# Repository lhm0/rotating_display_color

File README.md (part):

# Rotating Color Display

## Abstract: 
 The Rotating Color Display is a compact disc-sized device that rotates quietly using a CD motor. It features 56 color LEDs that display animated color images as well as time and weather data sourced from the internet. The device is wirelessly powered and controlled via a user-friendly web interface. It uses ESP32 and RP2040 microcontrollers, pre-manufactured boards, and is easy to assemble.

<p align="center"> 

</p> 

## 1. Description of the device

The Rotating Color Display device comprises two primary units: a power supply unit and a display board (**figure 1**). Both are circular in design, with a diameter of 120mm, similar to the dimensions of a standard Compact Disk. The display board is rotated by a CD motor. Energy is wirelessly transmitted from the power supply unit to the display board, eliminating the need for wired connections.

**Figure 1:  Rotating Color Display assembly.** The lower PCB is the power supply with wireless power transmission, the upper PCB is the display board.

The display board is equipped with a row containing 56 color LEDs. The LED operations are controlled by a RP2040 microcontroller, while an ESP32 microcontroller generates the display content. Images (including animated images) can be stored on and loaded from a micro SMD card. The ESP32 maintains a Wi-Fi connection to the internet.

This internet connection allows the device to retrieve the time from a time server, ensuring time accuracy. It also allows for the acquisition of weather data. Device operation is managed through a web interface (**figure 2**), accessible from any web browser. The interface allows users to manage login credentials, upload image files to the display, and control image and configuration files through a file manager.

**Figure 2:** The **web user interface** allows for operating mode selection and device configuration.

## 2. Operating modes

When switched on, the device tries to connect to a known wifi. If no valid wifi credentials are found, the unit will be configured as wifi access point. In this mode, a computer or mobile device can be connected, directly (SSID: RD40, no password). 

Once the wifi connection has been established, the unit will display its IP address on the  home page of the device (**figure 3**). Enter this address in your web browser. This will load the web user interface and will allow you to configure your local wifi.

**Figure 3: home page.**

There are several operating modes that display time and weather information (**figure 4**). The logo clock mode integrates a customizable image into the clock face. The image can be easily uploaded from the user interface. The same is true for the analog clock, which uses a customizable clock face in the background.

**Figure 4: operating modes.** Modes can be selected and configured through the web interface.

## 3. Mechanical design

The device consists of two assemblies: power supply and display. The power supply board is also the base plate, which can either be placed on a flat surface or hung on a wall. A standard CD motor is attached to this board so that the CD tray above the power supply board can accommodate the display assembly. The display board is fixed with two M2 x 6 mm screws. Furthermore, the base plate carries a potentiometer to control the motor speed as well as an on/off switch for the motor.

**Figure 5: Power Supply Board** with CD motor (middle), 12 - 24 V power jack (lower side), and speed potentiometer

An important requirement for the display board is that the center of mass of the unit is exactly in the middle, on the axis of rotation of the motor. This is the only way to ensure smooth and vibration-free running of the display. To achieve this, the electronic components are arranged symmetrically in three groups (**figure 7**). In the first group the components are arranged symmetrically to a vertical axis. This initially ensures that the center of gravity lies on this vertical axis. However, since the components cannot be distributed symmetrically to the horizontal axis of symmetry, the center of gravity must be shifted to the center along this axis using balancing weights. For this purpose, two M3x6mm screws with two nuts each are placed to the right and left of the ESP32 antenna. The second group of components is arranged symmetrically in respect to the center point of the disk and does not need a balancing weight, therefore. The third group, however, does need a balancing weight (M3 x 6, 1 nut) in the 4:30 position of the disk.The overall balancing result is very good, but can certainly be further optimized.

**Figure 6: Display Board.** Main components are the two LED rows, five serial shift register chips, and two microcontrollers (Arduino nano and ESP-01s). On the backside of the board the secondary coil of the wireless power supply is attached.

**Figure 7:** The components of the display board are arranged symmetrically in three groups. Balancing weights are used in group 1 and 3 to shift the center of gravity to the middle of the disk.

The LED row consists of 56 discrete, rectangular LEDs. The components each have a width of 1.6 mm and can be lined up with little spacing. The center of the LEDs is in a 2 mm grid. However, the row of LEDs is not arranged symmetrically to the center of the disk, but shifted by 0.5 mm. If the display panel is rotated by 180 degrees, this decentration causes the LEDs to be shifted by exactly 1 mm from the original grid (**figure 8**). This results in rotational interlacing: the radial resolution is increased from 2 to 1 mm. At the same time, the perceived frame rate also increases by a factor of 2..

**Figure 8:** The LED row is shifted radially by half a LED width. The two halfs of the row generate an interlacing effect, which doubles both the radial resolution and the image frame rate.

The LEDs must output the image information at exactly the right position with each rotation. For spatial alignment of the image, a trigger signal is generated at a defined position for each rotation, which triggers the sequential, clocked output of the pixels. The trigger signal must be spatially very stable, otherwise no smooth image can be generated. It turned out that a Hall sensor is best suited for this purpose. It is located between the two USB-C connectors (see **figure 6**, left picture, bottom edge of the PCB). The magnet is glued into a hole of the power supply PCB (see figure 5, right picture, 2 o'clock position).

## 4. Electronics architecture

The distribution of the electronic circuitry between the two assemblies is shown in **figure 9**. The power supply assembly contains a Royer converter for wireless power transfer to the display assembly and an adjustment of the motor speed. The 56 color LEDs of the display assembly are controlled by 7 shift registers (24 bits each), which in turn are supplied with clock and data by a RP2040 microcontroller via an SPI interface. The displayed content is generated by an ESP32-S3 microcontroller, which is connected to the internet via Wifi. Furthermore, image data can be loaded from a micro SD card. The ESP32 transmits its data to the RP2040 via a SPI interface.

**Figure 9: electronics schematics.**

## 5. Power supply board

The core of the power supply is a Royer converter for wireless power transfer. An excellent article on the operation and design of the circuit can be found at Mikrocontroller.net (German) and the circuit was taken from there. Two transistors are alternately switched (push pull operation) so that a current flows through one half of the coil at a time. The coil belongs to a resonant circuit with a resonant frequency of about 120 kHz. The control voltage for the transistors is obtained via a coupling coil (**figure 10**). The secondary coil is located below the display board (see **figure 6**, right).

The Royer circuit uses very few components. However, the coil is quite complex. It is a bifilar coil, where the two halves are interleaved. In addition, the coupling coil must be connected with the correct polarity, otherwise the two transistors will be destroyed. In the early stages of development, the coil was wound with copper wire. However, this solution was quite difficult to reproduce, so in the final design the coils (bifilar primary coil, coupling coil, secondary coil) were implemented as a printed circuit (see **figure 5**, right and **figure 6** right). The circuit was found to have surprisingly high and perfectly adequate transmission efficiency, although the quality factor of the printed coils is inevitably compromised. The Royer converter with the printed coil assembly is absolutely safe to rebuild.

The Royer converter can be supplied with 12 to 24 V. Depending on the voltage, the transferred power can be increased. This allows the operation of the display at high brightness. However, even with 12 V supply, the available power is sufficient for normal operation. 

**Figure 10: Royer converter**. Compare Mikrocontroller.net for reference.

There is also a circuit for supplying the CD motor on the power supply board (**figure 11**). As the supply voltage can be vary from 12 to 24 V, a step down converter is used to generate a variable voltage between 1.7V and 6.0V, which can be adjusted via a potentiometer. The voltage range corresponds to the specified operating range of the CD motor. The supply of the motor can be interrupted with a switch, for example to allow programming of the microcontrollers.

**Figure 11: variable voltage regulator** for driving the CD motor

## 6. Display Board

**a) The LEDs**

The 56 LEDs of the display board are driven by 7 cascaded 24-bit shift registers (**figure 12**). The registers load the serial data stream from one of the SPI interfaces of the RP2040. The microcontroller generates separate "LED enable" signal for the R, G, B LEDs, respectively. This allows for white balancing (not implemented yet). The STP24DP05BTR LED current sink controller sets the LED current to 20mA each. The maximum current per register would therefore be 480mA, if all LEDs were on, simultaneously and continuously. Theoretically, the current of the 56 LEDs could add up to 3.3A, which, at 5V, would correspond to 16.5 W. This is significantly beyond the capability of the wireless power supply. However, the current can be controlled by the RP2040 microcontroller by setting the duty cycle appropriately.

**Figure 12: circuit diagrams of the display board**. Diagrams also available as download and on Github.

**b) Displaying color**

Displaying color is based on additive color mixing. The three primary colors, red, green, and blue are mixed with different intensities. For example red and green combined at equal intensity make yellow. However, the circuit only allows the LEDs to be either on or off. Intensity can only be set using pulse width modulation. In order to synchronize PWM with the rotation of the disk, each pixel is devided into 8 sub-pixels (**figure 13**). This allows for setting the intensity in 8 steps for red, green, and blue, respectively. The color space can be displayed with 8 x 8 x 8 = 512 colors.

**Figure 13: displaying color**. each pixel is divided into 8 sub-pixels. This allows for pulse width modulation of the LED intensity. The intensity resolution is 8 steps for red, green, and blue, respectively. On the right hand side there is a photo of some of the pixels of the running display.

**c) RP2040 interrupts and timing**

The SPI interface is operated with a clock rate of 25 MHz. The 168 bits (56 RGB LEDs, 3 colors each) are therefore transferred in 168 x 1/25MHz = 6.7µs. Assuming a maximum rotation speed of the display of 1200 RPM, this corresponds to 50ms per revolution. At one full rotation of the display 240 pixels with 8 sub-pixels each are output per LED. This corresponds to 26µs per sub-pixel. Thus, the transmission time via the SPI bus (6.7µs) is significantly shorter than the display time per sub-pixel.

The idea of using two microcontrollers (RP2040 and ESP32-S3) is essentially to separate the very time-critical timing of the LED control from the computationally intensive and asynchronous image generation and internet communication. In this way, the RP2040 is relieved to the maximum and the display of the image is extremely stable.

The software of the RP2040 programmed in C consists of two short interrupt routines. The first routine ("HallIRQ") is triggered by the Hall sensor exactly once for each full rotation (**figure 14**). This routine starts a timer, which sets the duration for which a single row of 56 color pixels is displayed. Once the timer expires, it is automatically restarted and a second interrupt routine is triggered ("PixelIRQ"). In this second routine the bit pattern of the LEDs is updated. So in this way a new LED pattern appears with each expiration of the timer. It is important that the timer restarts automatically (hardware controlled). Otherwise there could be a delay if the processor cannot start the interrupt routine immediately (because another routine prevents this, for example).

Another important function is to set the duration of the timer 1 so that exactly 240 x 8 = 1920 pixel rows per turn are output. For this purpose, the variable "tpt" (time per turn) is increased by the set value of the timer with each call of PixelIRQ. The routine HallTRQ can read tpt and thus knows the exact time duration for one revolution - even if it consists of more or less than 1920 timer cycles. The new time per pixel (tpt/240) is then calculated from this value and the timer is set accordingly.

To control the image brightness of the red, green, and blue LEDs, the threshold function of the timer is used: as soon as a programmable threshold for R, G, and B is exceeded, an output of the RP2040 switches. The three signals are used to switch on the respective LEDs for the selected time. Controlling the brightness of R, G, and B separately allows to adjust the relative brightness of the three channels and therefore to shift the white point and thus color balancing the display. However, it has turned out that the LEDs are calibrated such that a reasonable "white" is achieved when the LED current is set to 20 mA for the three LEDs, respectively.

**Figure 14: RP2040 interrupt timing.** The timer clocks the pixel output and sets the LED brightness.

**d) ESP32-S3 for Internet communication and image generation**

The microcontroller ESP32 has a Wifi module for internet communication. The antenna of the controller is placed at the edge of the display board, because the interference field of the wireless power supply is lowest there. 

Although a concern in the beginning of the development, it turned out that the fast rotation of the display does not lead to any noticeable impairment of the Wifi connection.

**e) Programming of the microcontrollers**

The RP2040 can be programmed via a USB-C socket. During programming the power supply of the display needs to be on. Should there be a connection problem between the RP2040 and the programming computer, it helps to start the controller in boot mode. In order to do so, push and hold the RP2040 boot button while powering on the device. Once power is on, you can release the button.

Programming the ESP32S3 via its USB-C connector is easy and reliable as well. There is also a boot button, which can be used for initializing the controller.

Please note that the HTML, CSS and JS code of the user interface webpages has to be loaded onto the micro SD card. Make sure to properly formate (FAT16) the card before copying the data. You need to copy all files and folders in the "data" subfolder of the ESP32 directory of the repository to the root level of the SD card. When done, there. should be the folders "html", "variables", and "images" on the highest level of the SD card. 

# 7. The Software of the ESP32

The ESP-32 handles the generation of the image data and its transmission to the RP2040 (rouphly 10 times per second). The displayed information (time and weather data) is retrieved from the Internet or read from the SD card (still images and animated images). Furthermore, the microcontroller serves as a simple HTML web server that can be accessed by any browser to control the display.

**a) Generation of the image data**

Even though the resolution of the display achieved with the 56 color LEDs is relatively low, it is sufficient to display images and text upright, undistorted and therefore easily readable. The image data is generated in a rectangular pixel matrix (i.e. a cartesian coordinate system) with 110 x 110 pixels (**figure 15**). This bitmap then has to be transformed into the polar coordinate system of the rotating LED rows, before it is transferred to the RP2040. To make the transformation fast, a lookup table is used, which transforms the x,y coordinates of the bitmap into the r, theta coordinates of the rotating LED lines. The transformation also takes into account the alternating order of the LEDs between the two halfs of the row.

**Figure 15:** The display handles a **110x110 pixel bitmap**, which is transformed into the polar coordinate system of the rotating LED rows

**b) Control of the display via web interface**

For the implementation of the web server the library ESPAsyncWebServer is used. It has the advantage that the server activity runs in the background independent of other processes running simultaneously on the controller. The server retrieves the HTML, CSS and JS data of the displayed web pages from the SD card file system. Therefore, the web pages and the server can be implemented independently. Retrieving or modifying data is done using the HTTP GET and POST methods.

Certain parameters (brightness of the LEDs, operating mode of the display) can be set via the web interface. In addition, configuration data, such as the access data to the weather service openweather.org or the Wifi data can be edited and saved. These data are also stored in the file system of the SD card and are therefore also available after a reboot.

The user interface of the device has a file browser with which files can be uploaded from the end device (e.g. mobile device) to the SD card or downloaded from the SD card. This is especially usefull for loading image data to the device. In addition, files and entire directories can be deleted, renamed and moved. This simplifies the organization of the flash disk considerably.

Furthermore, the web interface provides a page for converting, uploading, and organizing images ("RDC Image Manager"). Still images can be uploaded in almost any image format and resolution. The software down scales and converts the images into the proprietary ".rdc" format ("rdc" = rotating display color). This format stores the color pixels sequentially, non-compressed, using 3 x 4 bits (1,5 bytes) per pixel. 

The RDC Image Manager can also deal with animated GIF files. As the image update rate is limited (about 10 images per second), there is an option to reduce the number of frames of the animated sequence. Please note, that saving an animated ".rdc" file might take a while, as the filesize can be substantial.

Known bug: the upload of animated ".rdc" files might lead to corrupt files, sometimes. The cause has not been clarified yet.

**c) Software architecture**

The ESP32 software is written in C++. In order to keep an overview despite the large amount of software, the function blocks and the data have been divided into classes. The following is a brief description of the most important classes:

Class RD40

The class provides the central rotating display object. It manages the (private) data of the displayed image (four bits per color and three colors per pixel). The class has methods for displaying bitmaps and for passing data to the display controller.

Class myBMP

This class creates 110x110 color bitmaps for display. It uses private methods to print text on the bitmap, draw lines and circles, or load images.

Class WebInterface

This class manages the web user interface. Once the webInterface object has been initiated, the web server will run in the background without the need for any attention from the software. The class provides certain attributes, such as clockMode and brightness, which are managed by the web interface. The user can change configuration data via the web interface. The data is then stored as parameter files on the SD card.

Not being a software engineer myself, the source code would most certainly benefit from a code review and revision.

**d) Development Environment**

Visual Studio Code with the PlatformIO extension was used as the development environment for both RP2040 and ESP32. The environment is much faster and more comfortable than the Arduino IDE. The ini files of the respective projects manages all settings, including libraries necessary for compiling. 
In addition, Visual Studio Code can also be used for the development of the source code of the web pages.

## 8. Reproduction of the rotating display

All necessary data, such as source code, circuit diagrams, printed board layouts, parts list and sources of supply are included either in this article or in my public github repository. They may be used for non-commercial purposes, such as by hobbyists or in education, whether for reproduction or further development. Either way, please respect the terms of the license.

The two main boards (display board and power supply board) can be manufactured based on the provided production data. The prototypes were manufactured and assembled by JLCPCB. The production data, including Gerber files, BOM, and component position files, are included in the repository. 

Some components need to be soldered manually, as they are through-hole-components. Please refer to the following description. The assembly is relatively simple, although some soldering skills are required. 

**Figure 16:** Start with the assembly of the power supply board. Use fast curing two component epoxy resin to glue the CD motor to the carrier plate. Furthermore, carefully glue two M2 nuts to the CD tray auxilliary plate, without contaminating the threats.

**Figure 17:** Use double sided tape to attache the auxilliary plate with the two M2 nuts to the back of the CD tray. By means of two M2 screws you can make sure the plate is in the right position.

**Figure 18:** Solder the through-hole components to the power supply board. Use 4-pin connectors to attach the motor assembly to the power supply pcb. Screw four 20 mm bolts to the pcb.

**Figure 19:** Glue rupper bumpers onto the bolts. Furthermore, glue the magnet into the respective hole in the power supply board. As the Hall sensor used can deal with any direction of the magnetic field, the orientation of the magnet does not matter.

**Figure 20:** Use 6 pins to attach the secondary coil pcb to the back of the display board. Make sure, the two boards are connected and soldered tensionlessly, as the relative position between the two boards needs to be as precise as possible. Finally, use two M2 x 6 screws to attach the display pcb to the power supply assembly.

## 9. Conclusions

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
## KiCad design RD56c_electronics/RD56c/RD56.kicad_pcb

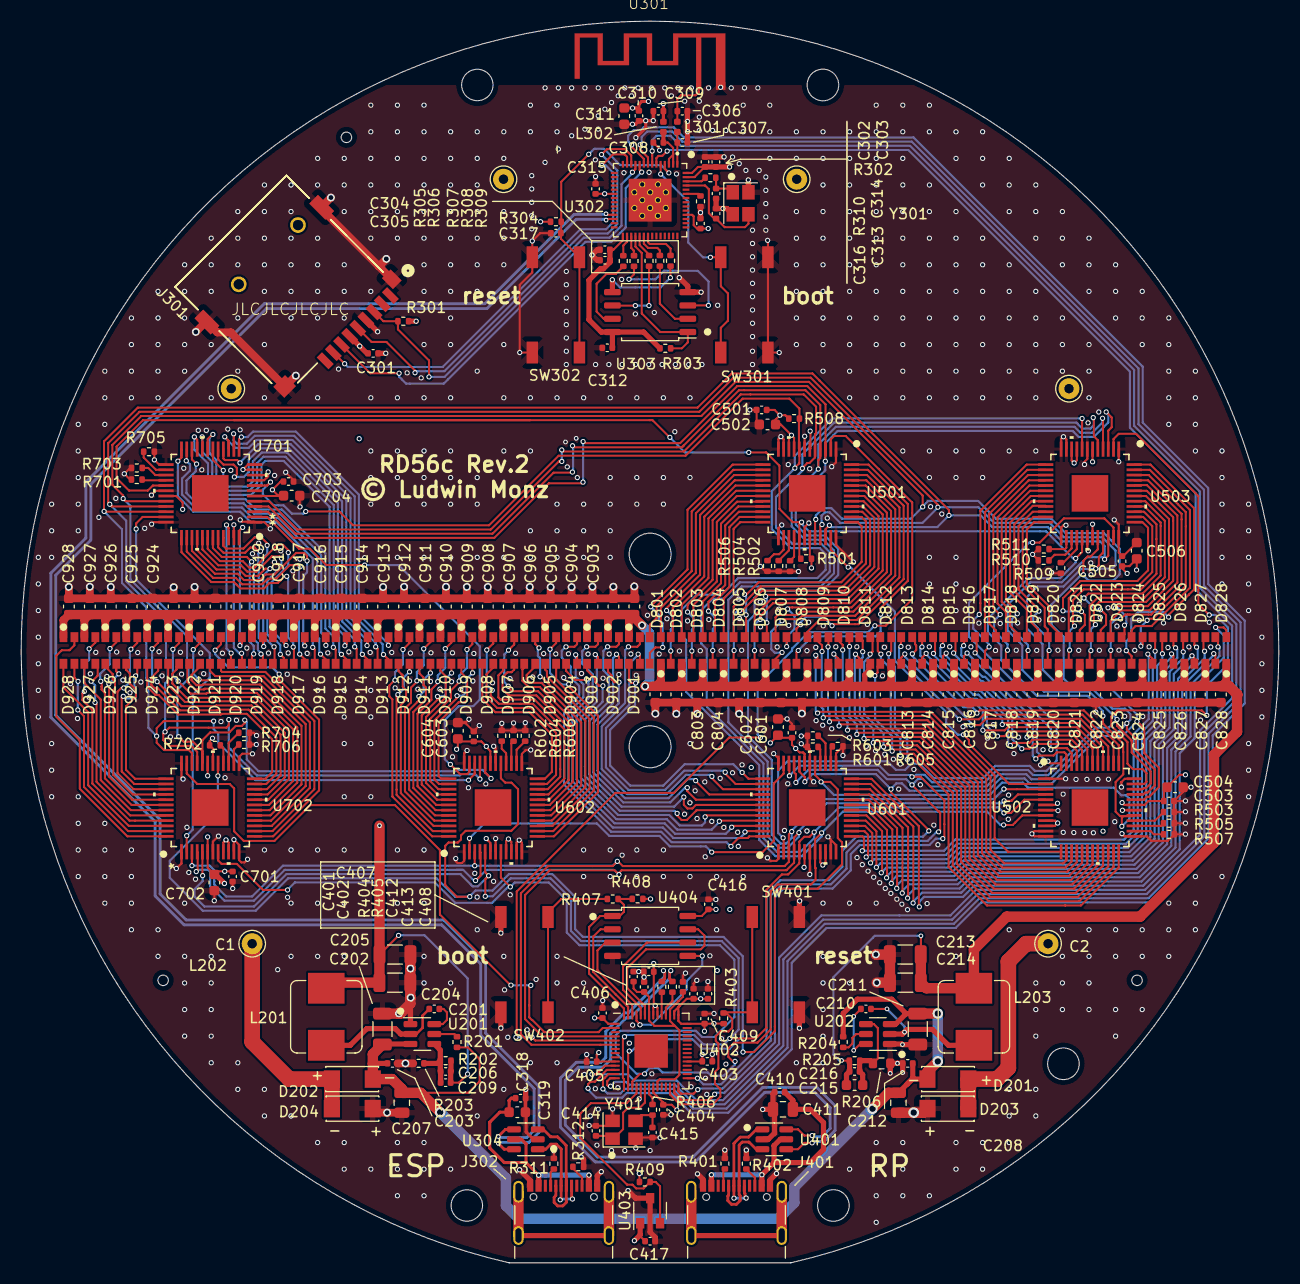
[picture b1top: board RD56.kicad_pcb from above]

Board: 4 copper layers, 120.1 x 118.6 mm, 263 parts (0 on the bottom side), 277 nets.

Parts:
C201, C203, C210, C212, C301, C304, C308, C309, C312, C315, C316, C318, C401, C402, C403, C404, C405, C406, C407, C408, C409, C410, C416, C417, C501, C503, C505, C601, C603, C701, C703: 100nF; C_0402_1005Metric
C202, C211: 10µF, 50V; C_1206_3216Metric
C204, C205, C213, C214: 22µF, 25V; C_1206_3216Metric
C206, C216: 47pF; C_0402_1005Metric
C207, C208: 22µF, 25V; C_0805_2012Metric
C209, C313, C314: 10pF; C_0402_1005Metric
C215: 30pF; C_0603_1608Metric
C302: 10nF; C_0402_1005Metric
C303, C305, C310, C317, C412, C413: 1µF; C_0402_1005Metric
C306, C307: 3p3; C_0402_1005Metric
C311, C319, C502, C504, C506, C602, C604, C702, C704, C801, C802, C803, C804, C805, C806, C807, C808, C809, C810, C811, C812, C813, C814, C815, C816, C817, C818, C819, C820, C821, C822, C823, C824, C825, C826, C827, C828, C901, C902, C903, C904, C905, C906, C907, C908, C909, C910, C911, C912, C913, C914, C915, C916, C917, C918, C919, C920, C921, C922, C923, C924, C925, C926, C927, C928: 10µF; C_0603_1608Metric
C411: 10µF; C_0805_2012Metric
C414, C415: 27pF; C_0402_1005Metric
D201, D202, D203, D204: SS34; DIOM7959X265N
D801, D802, D803, D804, D805, D806, D807, D808, D809, D810, D811, D812, D813, D814, D815, D816, D817, D818, D819, D820, D821, D822, D823, D824, D825, D826, D827, D828, D901, D902, D903, D904, D905, D906, D907, D908, D909, D910, D911, D912, D913, D914, D915, D916, D917, D918, D919, D920, D921, D922, D923, D924, D925, D926, D927, D928: LED_BARG; LED_RGB_1210
J301: Micro_SD_Card; microSD_SMD
J302, J401: USB_C_Receptacle_USB2.0; USB_C_Receptacle
L201, L203: 33µH; L_Bourns_SRP7028A_7.3x6.6mm
L202: Coil; coil_large
L301, L302: 2n2; L_0402_1005Metric
R201, R202, R204, R205, R303: 100k; R_0402_1005Metric
R203: 22k; R_0402_1005Metric
R206: 13k; R_0603_1608Metric
R301, R304, R310, R403, R501, R508: 10k; R_0402_1005Metric
R302: 22; R_0402_1005Metric
R305, R306, R307, R308, R309: 0; R_0402_1005Metric
R311, R312, R401, R402: 5k1; R_0402_1005Metric
R404, R405: 27R; R_0402_1005Metric
R406, R407, R502, R503, R504, R505, R506, R507, R509, R510, R511, R601, R602, R603, R604, R605, R606, R701, R702, R703, R704, R705, R706: 1k; R_0402_1005Metric
R408: do not fit; R_0402_1005Metric
R409: 20k; R_0402_1005Metric
SW301: boot; ROCPU_switch
SW302, SW401: reset; ROCPU_switch
SW402: USB boot; ROCPU_switch
U201, U202: TPS54202DDC; SOT-23-6
U301: PCB_antenna
U302: ESP32-S3; IC_ESP32-S3
U303, U404: W25Q128JVS; SOIC-8_5.23x5.23mm_P1.27mm
U304, U401: USBLC6-2SC6; SOT-23-6
U402: RP2040; QFN-56-1EP_7x7mm_P0.4mm_EP3.2x3.2mm
U403: MH253
U501, U502, U503, U601, U602, U701, U702: STP24DP05BTR; TQFP48-EP_STM
Y301: 40 MHz; Crystal_SMD_4Pin_3.2x2.5mm
Y401: 12MHz; Crystal_SMD_3225-4Pin_3.2x2.5mm

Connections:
+1V1: C401.2, C402.2, C412.2, U402.23 (DVDD), U402.45 (VREG_VOUT), U402.50 (DVDD)
+3.3V: C204.1, C205.1, C206.1, C209.1, C301.1, C302.1, C303.1, C309.1, C310.1, C311.1, C315.1, C316.1, C403.2, C404.2, C405.2, C406.2, C407.2, C408.2, C409.2, C413.2, C416.2, C417.1, C501.1, C502.1, C503.1, C504.1, C505.1, C506.1, C601.1, C602.1, C603.1, C604.1, C701.1, C702.1, C703.1, C704.1, J301.4 (VDD), L201.2, L302.2, R202.2, R301.1, R304.1, R403.2, R408.2, R409.1, R501.2, R508.1, U302.20 (VDD3P3_RTC), U302.46 (VDD3P3_CPU), U302.55 (VDDA1), U302.56 (VDDA2), U402.1 (IOVDD), U402.10 (IOVDD), U402.22 (IOVDD), U402.33 (IOVDD), U402.42 (IOVDD), U402.43 (ADC_AVDD), U402.44 (VREG_IN), U402.48 (USB_VDD), U402.49 (IOVDD), U403.1 (Vcc), U404.8 (VCC), U501.6 (VDD@1), U501.9 (DG), U501.10 (DF0), U501.31 (VDD@2), U502.6 (VDD@1), U502.9 (DG), U502.10 (DF0), U502.31 (VDD@2), U503.6 (VDD@1), U503.9 (DG), U503.10 (DF0), U503.31 (VDD@2), U601.6 (VDD@1), U601.9 (DG), U601.10 (DF0), U601.31 (VDD@2), U602.6 (VDD@1), U602.9 (DG), U602.10 (DF0), U602.31 (VDD@2), U701.6 (VDD@1), U701.9 (DG), U701.10 (DF0), U701.31 (VDD@2), U702.6 (VDD@1), U702.9 (DG), U702.10 (DF0), U702.31 (VDD@2)
+5V: C213.1, C214.1, C215.1, C216.1, C801.1, C802.1, C803.1, C804.1, C805.1, C806.1, C807.1, C808.1, C809.1, C810.1, C811.1, C812.1, C813.1, C814.1, C815.1, C816.1, C817.1, C818.1, C819.1, C820.1, C821.1, C822.1, C823.1, C824.1, C825.1, C826.1, C827.1, C828.1, C901.1, C902.1, C903.1, C904.1, C905.1, C906.1, C907.1, C908.1, C909.1, C910.1, C911.1, C912.1, C913.1, C914.1, C915.1, C916.1, C917.1, C918.1, C919.1, C920.1, C921.1, C922.1, C923.1, C924.1, C925.1, C926.1, C927.1, C928.1, D801.2 (A), D802.2 (A), D803.2 (A), D804.2 (A), D805.2 (A), D806.2 (A), D807.2 (A), D808.2 (A), D809.2 (A), D810.2 (A), D811.2 (A), D812.2 (A), D813.2 (A), D814.2 (A), D815.2 (A), D816.2 (A), D817.2 (A), D818.2 (A), D819.2 (A), D820.2 (A), D821.2 (A), D822.2 (A), D823.2 (A), D824.2 (A), D825.2 (A), D826.2 (A), D827.2 (A), D828.2 (A), D901.2 (A), D902.2 (A), D903.2 (A), D904.2 (A), D905.2 (A), D906.2 (A), D907.2 (A), D908.2 (A), D909.2 (A), D910.2 (A), D911.2 (A), D912.2 (A), D913.2 (A), D914.2 (A), D915.2 (A), D916.2 (A), D917.2 (A), D918.2 (A), D919.2 (A), D920.2 (A), D921.2 (A), D922.2 (A), D923.2 (A), D924.2 (A), D925.2 (A), D926.2 (A), D927.2 (A), D928.2 (A), L203.2, R205.2
/ESP32_S3/BOOT: SW301.1, U302.5 (GPIO0)
/ESP32_S3/EN: C317.1, R304.2, SW302.1, U302.4 (CHIP_PU)
/ESP32_S3/ESP_D+: J302.A6 (D+), J302.B6 (D+), U304.1 (I/O1)
/ESP32_S3/ESP_D-: J302.A7 (D-), J302.B7 (D-), U304.3 (I/O2)
/ESP32_S3/GPIO45: R310.1, U302.51 (GPIO45)
/ESP32_S3/LNA: C307.1, L301.2, U302.1 (LNA_IN)
/ESP32_S3/SPI3_CS0: J301.2 (DAT3/CD), U302.13 (GPIO8)
/ESP32_S3/SPI3_MISO: J301.7 (DAT0), R301.2, U302.11 (GPIO6)
/ESP32_S3/SPI3_MOSI: J301.3 (CMD), U302.10 (GPIO5)
/ESP32_S3/SPI3_SCK: J301.5 (CLK), U302.12 (GPIO7)
/ESP32_S3/SPICLK: R307.1, U303.6 (CLK)
/ESP32_S3/SPICLK_: R307.2, U302.33 (SPICLK)
/ESP32_S3/SPICS0: R303.1, U302.32 (SPICS0), U303.1 (~CS)
/ESP32_S3/SPID: R309.1, U303.5 (DI(IO0))
/ESP32_S3/SPID_: R309.2, U302.35 (SPID)
/ESP32_S3/SPIHD: R305.1, U303.7 (IO3)
/ESP32_S3/SPIHD_: R305.2, U302.30 (SPIHD)
/ESP32_S3/SPIQ: R308.1, U303.2 (DO(IO1))
/ESP32_S3/SPIQ_: R308.2, U302.34 (SPIQ)
/ESP32_S3/SPIWP: R306.1, U303.3 (IO2)
/ESP32_S3/SPIWP_: R306.2, U302.31 (SPIWP)
/ESP32_S3/UD_ESP+: U302.26 (GPIO20), U304.6 (I/O1)
/ESP32_S3/UD_ESP-: U302.25 (GPIO19), U304.4 (I/O2)
/ESP32_S3/VBUS3: C318.2, C319.1, J302.A4 (VBUS), J302.A9 (VBUS), J302.B4 (VBUS), J302.B9 (VBUS), U304.5 (VBUS)
/ESP32_S3/VDD3P3: C308.1, L302.1, U302.2 (VDD3P3), U302.3 (VDD3P3)
/ESP32_S3/VDD_SPI: C304.1, C305.1, C312.2, R303.2, U302.29 (VDD_SPI), U303.8 (VCC)
/ESP32_S3/XTAL_N: C313.1, U302.53 (XTAL_N), Y301.3
/ESP32_S3/XTAL_P: R302.2, U302.54 (XTAL_P)
/ESP32_S3/XTAL_Pp: C314.1, R302.1, Y301.1
/ESP32_S3/feed: C306.1, L301.1, U301.2 (feed)
/LED_electronics1/REXTB4: R605.1, U601.26 (REXTB)
/LED_electronics1/REXTB5: R606.1, U602.26 (REXTB)
/LED_electronics1/REXTG4: R603.1, U601.27 (REXTG)
/LED_electronics1/REXTG5: R604.1, U602.27 (REXTG)
/LED_electronics1/REXTR4: R601.1, U601.28 (REXTR)
/LED_electronics1/REXTR5: R602.1, U602.28 (REXTR)
/LED_electronics1/SD4: U601.35 (SDO), U602.2 (SDI)
/LED_electronics2/REXTB4: R705.1, U701.26 (REXTB)
/LED_electronics2/REXTB5: R706.1, U702.26 (REXTB)
/LED_electronics2/REXTG4: R703.1, U701.27 (REXTG)
/LED_electronics2/REXTG5: R704.1, U702.27 (REXTG)
/LED_electronics2/REXTR4: R701.1, U701.28 (REXTR)
/LED_electronics2/REXTR5: R702.1, U702.28 (REXTR)
/LED_electronics2/SD6: U701.35 (SDO), U702.2 (SDI)
/LED_electronics/REXTB1: R506.1, U501.26 (REXTB)
/LED_electronics/REXTB2: R507.1, U502.26 (REXTB)
/LED_electronics/REXTB3: R511.1, U503.26 (REXTB)
/LED_electronics/REXTG1: R504.1, U501.27 (REXTG)
/LED_electronics/REXTG2: R505.1, U502.27 (REXTG)
/LED_electronics/REXTG3: R510.1, U503.27 (REXTG)
/LED_electronics/REXTR1: R502.1, U501.28 (REXTR)
/LED_electronics/REXTR2: R503.1, U502.28 (REXTR)
/LED_electronics/REXTR3: R509.1, U503.28 (REXTR)
/LED_electronics/SD1: U501.35 (SDO), U502.2 (SDI)
/LED_electronics/SD2: U502.35 (SDO), U503.2 (SDI)
/RP2040/Hall: R409.2, U402.18 (GPIO15), U403.2 (Output)
/RP2040/QSPI_SCLK: U402.52 (QSPI_SCLK), U404.6 (CLK)
/RP2040/QSPI_SD0: U402.53 (QSPI_SD0), U404.5 (DI(IO0))
/RP2040/QSPI_SD1: U402.55 (QSPI_SD1), U404.2 (DO(IO1))
/RP2040/QSPI_SD2: U402.54 (QSPI_SD2), U404.3 (IO2)
/RP2040/QSPI_SD3: U402.51 (QSPI_SD3), U404.7 (IO3)
/RP2040/QSPI_SS: R407.2, R408.1, U402.56 (QSPI_SS), U404.1 (~CS)
/RP2040/RP_D+: J401.A6 (D+), J401.B6 (D+), U401.1 (I/O1)
/RP2040/RP_D-: J401.A7 (D-), J401.B7 (D-), U401.3 (I/O2)
/RP2040/RUN: R403.1, SW401.2, U402.26 (RUN)
/RP2040/UD_2040+: R404.1, U401.6 (I/O1)
/RP2040/UD_2040++: R404.2, U402.47 (USB_DP)
/RP2040/UD_2040-: R405.1, U401.4 (I/O2)
/RP2040/UD_2040--: R405.2, U402.46 (USB_DM)
/RP2040/VBUS4: C410.2, C411.1, J401.A4 (VBUS), J401.A9 (VBUS), J401.B4 (VBUS), J401.B9 (VBUS), U401.5 (VBUS)
/RP2040/XIN: C414.2, U402.20 (XIN), Y401.1
/RP2040/XOUT: C415.1, R406.1, Y401.3
/RP2040/XOUT_: R406.2, U402.21 (XOUT)
/power supply/EN_BC1: R201.2, U201.5 (EN)
/power supply/EN_BC2: R204.2, U202.5 (EN)
/power supply/FB_BC1: C206.2, C209.2, R202.1, R203.2, U201.4 (FB)
/power supply/FB_BC2: C215.2, C216.2, R205.1, R206.2, U202.4 (FB)
/power supply/SW_BC1: C201.2, L201.1, U201.2 (SW)
/power supply/SW_BC2: C210.2, L203.1, U202.2 (SW)
/power supply/U_unreg: C202.1, C203.1, C207.1, C208.1, C211.1, C212.1, D201.1 (K), D202.1 (K), R201.1, R204.1, U201.3 (VIN), U202.3 (VIN)
/power supply/boot_BC1: C201.1, U201.6 (BOOT)
/power supply/boot_BC2: C210.1, U202.6 (BOOT)
/power supply/coil1: D202.2 (A), D204.1 (K), L202.1
/power supply/coil2: D201.2 (A), D203.1 (K), L202.2
DM: U402.15 (GPIO12), U501.5 (DM), U502.5 (DM), U503.5 (DM), U601.5 (DM), U602.5 (DM), U701.5 (DM), U702.5 (DM)
EF: R501.1, U402.16 (GPIO13), U501.29 (EF), U502.29 (EF), U503.29 (EF), U601.29 (EF), U602.29 (EF), U701.29 (EF), U702.29 (EF)
GND: C202.2, C203.2, C204.2, C205.2, C207.2, C208.2, C211.2, C212.2, C213.2, C214.2, C301.2, C302.2, C303.2, C304.2, C305.2, C306.2, C307.2, C308.2, C309.2, C310.2, C311.2, C312.1, C313.2, C314.2, C315.2, C316.2, C317.2, C318.1, C319.2, C401.1, C402.1, C403.1, C404.1, C405.1, C406.1, C407.1, C408.1, C409.1, C410.1, C411.2, C412.1, C413.1, C414.1, C415.2, C416.1, C417.2, C501.2, C502.2, C503.2, C504.2, C505.2, C506.2, C601.2, C602.2, C603.2, C604.2, C701.2, C702.2, C703.2, C704.2, C801.2, C802.2, C803.2, C804.2, C805.2, C806.2, C807.2, C808.2, C809.2, C810.2, C811.2, C812.2, C813.2, C814.2, C815.2, C816.2, C817.2, C818.2, C819.2, C820.2, C821.2, C822.2, C823.2, C824.2, C825.2, C826.2, C827.2, C828.2, C901.2, C902.2, C903.2, C904.2, C905.2, C906.2, C907.2, C908.2, C909.2, C910.2, C911.2, C912.2, C913.2, C914.2, C915.2, C916.2, C917.2, C918.2, C919.2, C920.2, C921.2, C922.2, C923.2, C924.2, C925.2, C926.2, C927.2, C928.2, D203.2 (A), D204.2 (A), J301.6 (VSS), J301.10 (S), J301.11 (S), J301.12 (S), J301.13 (S), J302.A1 (GND), J302.A12 (GND), J302.B1 (GND), J302.B12 (GND), J401.A1 (GND), J401.A12 (GND), J401.B1 (GND), J401.B12 (GND), R203.1, R206.1, R310.2, R311.2, R312.2, R401.2, R402.2, R502.2, R503.2, R504.2, R505.2, R506.2, R507.2, R509.2, R510.2, R511.2, R601.2, R602.2, R603.2, R604.2, R605.2, R606.2, R701.2, R702.2, R703.2, R704.2, R705.2, R706.2, SW301.2, SW302.2, SW401.1, SW402.1, U201.1 (GND), U202.1 (GND), U301.1 (GND), U302.57 (GND), U302.58, U302.59, U302.60, U302.61, U302.62, U302.63, U302.64, U302.65, U302.66, U302.67, U302.68, U302.69, U303.4 (GND), U304.2 (GND), U401.2 (GND), U402.19 (TESTEN), U402.57 (GND), U403.3 (Ground), U404.4 (GND), U501.1 (GND@1), U501.7 (GND@2), U501.11 (DF1), U501.12 (GND@3), U501.25 (GND@4), U501.30 (GND@5), U501.36 (GND@6), U502.1 (GND@1), U502.7 (GND@2), U502.11 (DF1), U502.12 (GND@3), U502.25 (GND@4), U502.30 (GND@5), U502.36 (GND@6), U503.1 (GND@1), U503.7 (GND@2), U503.11 (DF1), U503.12 (GND@3), U503.25 (GND@4), U503.30 (GND@5), U503.36 (GND@6), U601.1 (GND@1), U601.7 (GND@2), U601.11 (DF1), U601.12 (GND@3), U601.25 (GND@4), U601.30 (GND@5), U601.36 (GND@6), U602.1 (GND@1), U602.7 (GND@2), U602.11 (DF1), U602.12 (GND@3), U602.25 (GND@4), U602.30 (GND@5), U602.36 (GND@6), U701.1 (GND@1), U701.7 (GND@2), U701.11 (DF1), U701.12 (GND@3), U701.25 (GND@4), U701.30 (GND@5), U701.36 (GND@6), U702.1 (GND@1), U702.7 (GND@2), U702.11 (DF1), U702.12 (GND@3), U702.25 (GND@4), U702.30 (GND@5), U702.36 (GND@6), Y301.2, Y301.4, Y401.2, Y401.4
LE: U402.6 (GPIO4), U501.3 (LE/DM), U502.3 (LE/DM), U503.3 (LE/DM), U601.3 (LE/DM), U602.3 (LE/DM), U701.3 (LE/DM), U702.3 (LE/DM)
LED_B00: D801.1 (BK), U501.15 (B1)
LED_B01: D802.1 (BK), U501.18 (B2)
LED_B02: D803.1 (BK), U501.21 (B3)
LED_B03: D804.1 (BK), U501.24 (B4)
LED_B04: D805.1 (BK), U501.37 (B5)
LED_B05: D806.1 (BK), U501.40 (B6)
LED_B06: D807.1 (BK), U501.43 (B7)
LED_B07: D808.1 (BK), U501.46 (B8)
LED_B08: D809.1 (BK), U502.15 (B1)
LED_B09: D810.1 (BK), U502.18 (B2)
LED_B10: D811.1 (BK), U502.21 (B3)
LED_B11: D812.1 (BK), U502.24 (B4)
LED_B12: D813.1 (BK), U502.37 (B5)
LED_B13: D814.1 (BK), U502.40 (B6)
LED_B14: D815.1 (BK), U502.43 (B7)
LED_B15: D816.1 (BK), U502.46 (B8)
LED_B16: D817.1 (BK), U503.15 (B1)
LED_B17: D818.1 (BK), U503.18 (B2)
LED_B18: D819.1 (BK), U503.21 (B3)
LED_B19: D820.1 (BK), U503.24 (B4)
LED_B20: D821.1 (BK), U503.37 (B5)
LED_B21: D822.1 (BK), U503.40 (B6)
LED_B22: D823.1 (BK), U503.43 (B7)
LED_B23: D824.1 (BK), U503.46 (B8)
LED_B24: D825.1 (BK), U601.15 (B1)
LED_B25: D826.1 (BK), U601.18 (B2)
LED_B26: D827.1 (BK), U601.21 (B3)
LED_B27: D828.1 (BK), U601.24 (B4)
LED_B28: D901.1 (BK), U601.37 (B5)
LED_B29: D902.1 (BK), U601.40 (B6)
LED_B30: D903.1 (BK), U601.43 (B7)
LED_B31: D904.1 (BK), U601.46 (B8)
LED_B32: D905.1 (BK), U602.15 (B1)
LED_B33: D906.1 (BK), U602.18 (B2)
LED_B34: D907.1 (BK), U602.21 (B3)
LED_B35: D908.1 (BK), U602.24 (B4)
LED_B36: D909.1 (BK), U602.37 (B5)
LED_B37: D910.1 (BK), U602.40 (B6)
LED_B38: D911.1 (BK), U602.43 (B7)
LED_B39: D912.1 (BK), U602.46 (B8)
LED_B40: D913.1 (BK), U701.15 (B1)
LED_B41: D914.1 (BK), U701.18 (B2)
LED_B42: D915.1 (BK), U701.21 (B3)
LED_B43: D916.1 (BK), U701.24 (B4)
LED_B44: D917.1 (BK), U701.37 (B5)
LED_B45: D918.1 (BK), U701.40 (B6)
LED_B46: D919.1 (BK), U701.43 (B7)
LED_B47: D920.1 (BK), U701.46 (B8)
LED_B48: D921.1 (BK), U702.15 (B1)
LED_B49: D922.1 (BK), U702.18 (B2)
LED_B50: D923.1 (BK), U702.21 (B3)
LED_B51: D924.1 (BK), U702.24 (B4)
LED_B52: D925.1 (BK), U702.37 (B5)
LED_B53: D926.1 (BK), U702.40 (B6)
LED_B54: D927.1 (BK), U702.43 (B7)
LED_B55: D928.1 (BK), U702.46 (B8)
LED_G00: D801.4 (GK), U501.14 (G1)
LED_G01: D802.4 (GK), U501.17 (G2)
LED_G02: D803.4 (GK), U501.20 (G3)
LED_G03: D804.4 (GK), U501.23 (G4)
LED_G04: D805.4 (GK), U501.38 (G5)
LED_G05: D806.4 (GK), U501.41 (G6)
LED_G06: D807.4 (GK), U501.44 (G7)
LED_G07: D808.4 (GK), U501.47 (G8)
LED_G08: D809.4 (GK), U502.14 (G1)
LED_G09: D810.4 (GK), U502.17 (G2)
LED_G10: D811.4 (GK), U502.20 (G3)
LED_G11: D812.4 (GK), U502.23 (G4)
LED_G12: D813.4 (GK), U502.38 (G5)
LED_G13: D814.4 (GK), U502.41 (G6)
LED_G14: D815.4 (GK), U502.44 (G7)
LED_G15: D816.4 (GK), U502.47 (G8)
LED_G16: D817.4 (GK), U503.14 (G1)
LED_G17: D818.4 (GK), U503.17 (G2)
LED_G18: D819.4 (GK), U503.20 (G3)
LED_G19: D820.4 (GK), U503.23 (G4)
LED_G20: D821.4 (GK), U503.38 (G5)
LED_G21: D822.4 (GK), U503.41 (G6)
LED_G22: D823.4 (GK), U503.44 (G7)
LED_G23: D824.4 (GK), U503.47 (G8)
LED_G24: D825.4 (GK), U601.14 (G1)
LED_G25: D826.4 (GK), U601.17 (G2)
LED_G26: D827.4 (GK), U601.20 (G3)
LED_G27: D828.4 (GK), U601.23 (G4)
LED_G28: D901.4 (GK), U601.38 (G5)
LED_G29: D902.4 (GK), U601.41 (G6)
LED_G30: D903.4 (GK), U601.44 (G7)
LED_G31: D904.4 (GK), U601.47 (G8)
LED_G32: D905.4 (GK), U602.14 (G1)
LED_G33: D906.4 (GK), U602.17 (G2)
LED_G34: D907.4 (GK), U602.20 (G3)
LED_G35: D908.4 (GK), U602.23 (G4)
LED_G36: D909.4 (GK), U602.38 (G5)
LED_G37: D910.4 (GK), U602.41 (G6)
LED_G38: D911.4 (GK), U602.44 (G7)
LED_G39: D912.4 (GK), U602.47 (G8)
LED_G40: D913.4 (GK), U701.14 (G1)
LED_G41: D914.4 (GK), U701.17 (G2)
LED_G42: D915.4 (GK), U701.20 (G3)
LED_G43: D916.4 (GK), U701.23 (G4)
LED_G44: D917.4 (GK), U701.38 (G5)
LED_G45: D918.4 (GK), U701.41 (G6)
LED_G46: D919.4 (GK), U701.44 (G7)
LED_G47: D920.4 (GK), U701.47 (G8)
LED_G48: D921.4 (GK), U702.14 (G1)
LED_G49: D922.4 (GK), U702.17 (G2)
LED_G50: D923.4 (GK), U702.20 (G3)
LED_G51: D924.4 (GK), U702.23 (G4)
LED_G52: D925.4 (GK), U702.38 (G5)
LED_G53: D926.4 (GK), U702.41 (G6)
LED_G54: D927.4 (GK), U702.44 (G7)
LED_G55: D928.4 (GK), U702.47 (G8)
LED_R00: D801.3 (RK), U501.13 (R1)
LED_R01: D802.3 (RK), U501.16 (R2)
LED_R02: D803.3 (RK), U501.19 (R3)
LED_R03: D804.3 (RK), U501.22 (R4)
LED_R04: D805.3 (RK), U501.39 (R5)
LED_R05: D806.3 (RK), U501.42 (R6)
LED_R06: D807.3 (RK), U501.45 (R7)
LED_R07: D808.3 (RK), U501.48 (R8)
LED_R08: D809.3 (RK), U502.13 (R1)
LED_R09: D810.3 (RK), U502.16 (R2)
LED_R10: D811.3 (RK), U502.19 (R3)
LED_R11: D812.3 (RK), U502.22 (R4)
LED_R12: D813.3 (RK), U502.39 (R5)
LED_R13: D814.3 (RK), U502.42 (R6)
LED_R14: D815.3 (RK), U502.45 (R7)
LED_R15: D816.3 (RK), U502.48 (R8)
LED_R16: D817.3 (RK), U503.13 (R1)
LED_R17: D818.3 (RK), U503.16 (R2)
LED_R18: D819.3 (RK), U503.19 (R3)
LED_R19: D820.3 (RK), U503.22 (R4)
LED_R20: D821.3 (RK), U503.39 (R5)
LED_R21: D822.3 (RK), U503.42 (R6)
LED_R22: D823.3 (RK), U503.45 (R7)
LED_R23: D824.3 (RK), U503.48 (R8)
LED_R24: D825.3 (RK), U601.13 (R1)
LED_R25: D826.3 (RK), U601.16 (R2)
LED_R26: D827.3 (RK), U601.19 (R3)
LED_R27: D828.3 (RK), U601.22 (R4)
LED_R28: D901.3 (RK), U601.39 (R5)
LED_R29: D902.3 (RK), U601.42 (R6)
LED_R30: D903.3 (RK), U601.45 (R7)
LED_R31: D904.3 (RK), U601.48 (R8)
LED_R32: D905.3 (RK), U602.13 (R1)
LED_R33: D906.3 (RK), U602.16 (R2)
LED_R34: D907.3 (RK), U602.19 (R3)
LED_R35: D908.3 (RK), U602.22 (R4)
LED_R36: D909.3 (RK), U602.39 (R5)
LED_R37: D910.3 (RK), U602.42 (R6)
LED_R38: D911.3 (RK), U602.45 (R7)
LED_R39: D912.3 (RK), U602.48 (R8)
LED_R40: D913.3 (RK), U701.13 (R1)
LED_R41: D914.3 (RK), U701.16 (R2)
LED_R42: D915.3 (RK), U701.19 (R3)
LED_R43: D916.3 (RK), U701.22 (R4)
LED_R44: D917.3 (RK), U701.39 (R5)
LED_R45: D918.3 (RK), U701.42 (R6)
LED_R46: D919.3 (RK), U701.45 (R7)
LED_R47: D920.3 (RK), U701.48 (R8)
LED_R48: D921.3 (RK), U702.13 (R1)
LED_R49: D922.3 (RK), U702.16 (R2)
LED_R50: D923.3 (RK), U702.19 (R3)
LED_R51: D924.3 (RK), U702.22 (R4)
LED_R52: D925.3 (RK), U702.39 (R5)
LED_R53: D926.3 (RK), U702.42 (R6)
LED_R54: D927.3 (RK), U702.45 (R7)
LED_R55: D928.3 (RK), U702.48 (R8)
unnamed: J302.A5 (CC1), R311.1
unnamed: J302.B5 (CC2), R312.1
unnamed: J401.A5 (CC1), R401.1
unnamed: J401.B5 (CC2), R402.1
unnamed: R407.1, SW402.2
PWM0_A: U402.27 (GPIO16), U501.34 (OE-R), U502.34 (OE-R), U503.34 (OE-R), U601.34 (OE-R), U602.34 (OE-R), U701.34 (OE-R), U702.34 (OE-R)
PWM0_B: U402.28 (GPIO17), U501.33 (OE-G), U502.33 (OE-G), U503.33 (OE-G), U601.33 (OE-G), U602.33 (OE-G), U701.33 (OE-G), U702.33 (OE-G)
PWM1_A: U402.29 (GPIO18), U501.32 (OE-B), U502.32 (OE-B), U503.32 (OE-B), U601.32 (OE-B), U602.32 (OE-B), U701.32 (OE-B), U702.32 (OE-B)
RP_SPI0_MISO: U402.2 (GPIO0), U702.35 (SDO)
RP_SPI0_MOSI: U402.5 (GPIO3), U501.2 (SDI)
RP_SPI0_SCK: U402.4 (GPIO2), U501.4 (CLK), U502.4 (CLK), U503.4 (CLK), U601.4 (CLK), U602.4 (CLK), U701.4 (CLK), U702.4 (CLK)
RP_SPI1_CS0: U302.9 (GPIO4), U402.12 (GPIO9)
RP_SPI1_MISO: U302.7 (GPIO2), U402.14 (GPIO11)
RP_SPI1_MOSI: U302.6 (GPIO1), U402.11 (GPIO8)
RP_SPI1_SCK: U302.8 (GPIO3), U402.13 (GPIO10)
SD3: U503.35 (SDO), U601.2 (SDI)
SD5: U602.35 (SDO), U701.2 (SDI)
TF: R508.2, U402.17 (GPIO14), U501.8 (TF), U502.8 (TF), U503.8 (TF), U601.8 (TF), U602.8 (TF), U701.8 (TF), U702.8 (TF)

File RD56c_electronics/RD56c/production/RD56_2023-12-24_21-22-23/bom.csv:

Designator,Footprint,Quantity,Value,LCSC Part #
"C201, C203, C210, C212, C301, C304, C308, C309, C312, C315, C316, C318, C401, C402, C403, C404, C405, C406, C407, C408, C409, C410, C416, C417, C501, C503, C505, C601, C603, C701, C703",0402,31,100nF,C307331
"C202, C211",1206,2,"10µF, 50V",C13585
"C204, C205, C213, C214",1206,4,"22µF, 25V",C12891
"C206, C216",0402,2,47pF,C1567
"C207, C208",0805,2,"22µF, 25V",C45783
"C209, C313, C314",0402,3,10pF,C32949
C215,0603,1,30pF,C1658
C302,0402,1,10nF,C15195
"C303, C305, C310, C317, C412, C413",0402,6,1µF,C52923
"C306, C307",0402,2,3p3,C1565
"C311, C319, C502, C504, C506, C602, C604, C702, C704, C801, C802, C803, C804, C805, C806, C807, C808, C809, C810, C811, C812, C813, C814, C815, C816, C817, C818, C819, C820, C821, C822, C823, C824, C825, C826, C827, C828, C901, C902, C903, C904, C905, C906, C907, C908, C909, C910, C911, C912, C913, C914, C915, C916, C917, C918, C919, C920, C921, C922, C923, C924, C925, C926, C927, C928",0603,65,10µF,C96446
C411,0805,1,10µF,C15850
"C414, C415",0402,2,27pF,C1557
"D201, D202, D203, D204",DIOM7959X265N,4,SS34,C8678
"D801, D802, D803, D804, D805, D806, D807, D808, D809, D810, D811, D812, D813, D814, D815, D816, D817, D818, D819, D820, D821, D822, D823, D824, D825, D826, D827, D828, D901, D902, D903, D904, D905, D906, D907, D908, D909, D910, D911, D912, D913, D914, D915, D916, D917, D918, D919, D920, D921, D922, D923, D924, D925, D926, D927, D928",LED_RGB_1210,56,LED_BARG,C513366
J301,microSD_SMD,1,Micro_SD_Card,C5155564
"J302, J401",USB_C_Receptacle,2,USB_C_Receptacle_USB2.0,C709357
"L201, L203",L_Bourns_SRP7028A_7.3x6.6mm,2,33µH,C177245
L202,coil_large,1,Coil,
"L301, L302",0402,2,2n2,C412264
"R201, R202, R204, R205, R303",0402,5,100k,C25741
R203,0402,1,22k,C25768
R206,0603,1,13k,C22797
"R301, R304, R310, R403, R501, R508",0402,6,10k,C25744
R302,0402,1,22,C25092
"R305, R306, R307, R308, R309",0402,5,0,C17168
"R311, R312, R401, R402",0402,4,5k1,C25905
"R404, R405",0402,2,27R,C321419
"R406, R407, R502, R503, R504, R505, R506, R507, R509, R510, R511, R601, R602, R603, R604, R605, R606, R701, R702, R703, R704, R705, R706",0402,23,1k,C11702
R408,0402,1,do not fit,
R409,0402,1,20k,C25765
SW301,ROCPU_switch,1,boot,C5381238
"SW302, SW401",ROCPU_switch,2,reset,C5381238
SW402,ROCPU_switch,1,USB boot,C5381238
"U201, U202",SOT-23-6,2,TPS54202DDC,C191884
U301,PCB_antenna,1,~,
U302,IC_ESP32-S3,1,ESP32-S3,C2913192
"U303, U404",SOIC-8_5.23x5.23mm_P1.27mm,2,W25Q128JVS,C97521
"U304, U401",SOT-23-6,2,USBLC6-2SC6,C2687116
U402,QFN-56-1EP_7x7mm_P0.4mm_EP3.2x3.2mm,1,RP2040,C2040
U403,MH253,1,MH253,
"U501, U502, U503, U601, U602, U701, U702",TQFP48-EP_STM,7,STP24DP05BTR,C157417
Y301,Crystal_SMD_4Pin_3.2x2.5mm,1,40 MHz,C379787
Y401,Crystal_SMD_3225-4Pin_3.2x2.5mm,1,12MHz,C9002

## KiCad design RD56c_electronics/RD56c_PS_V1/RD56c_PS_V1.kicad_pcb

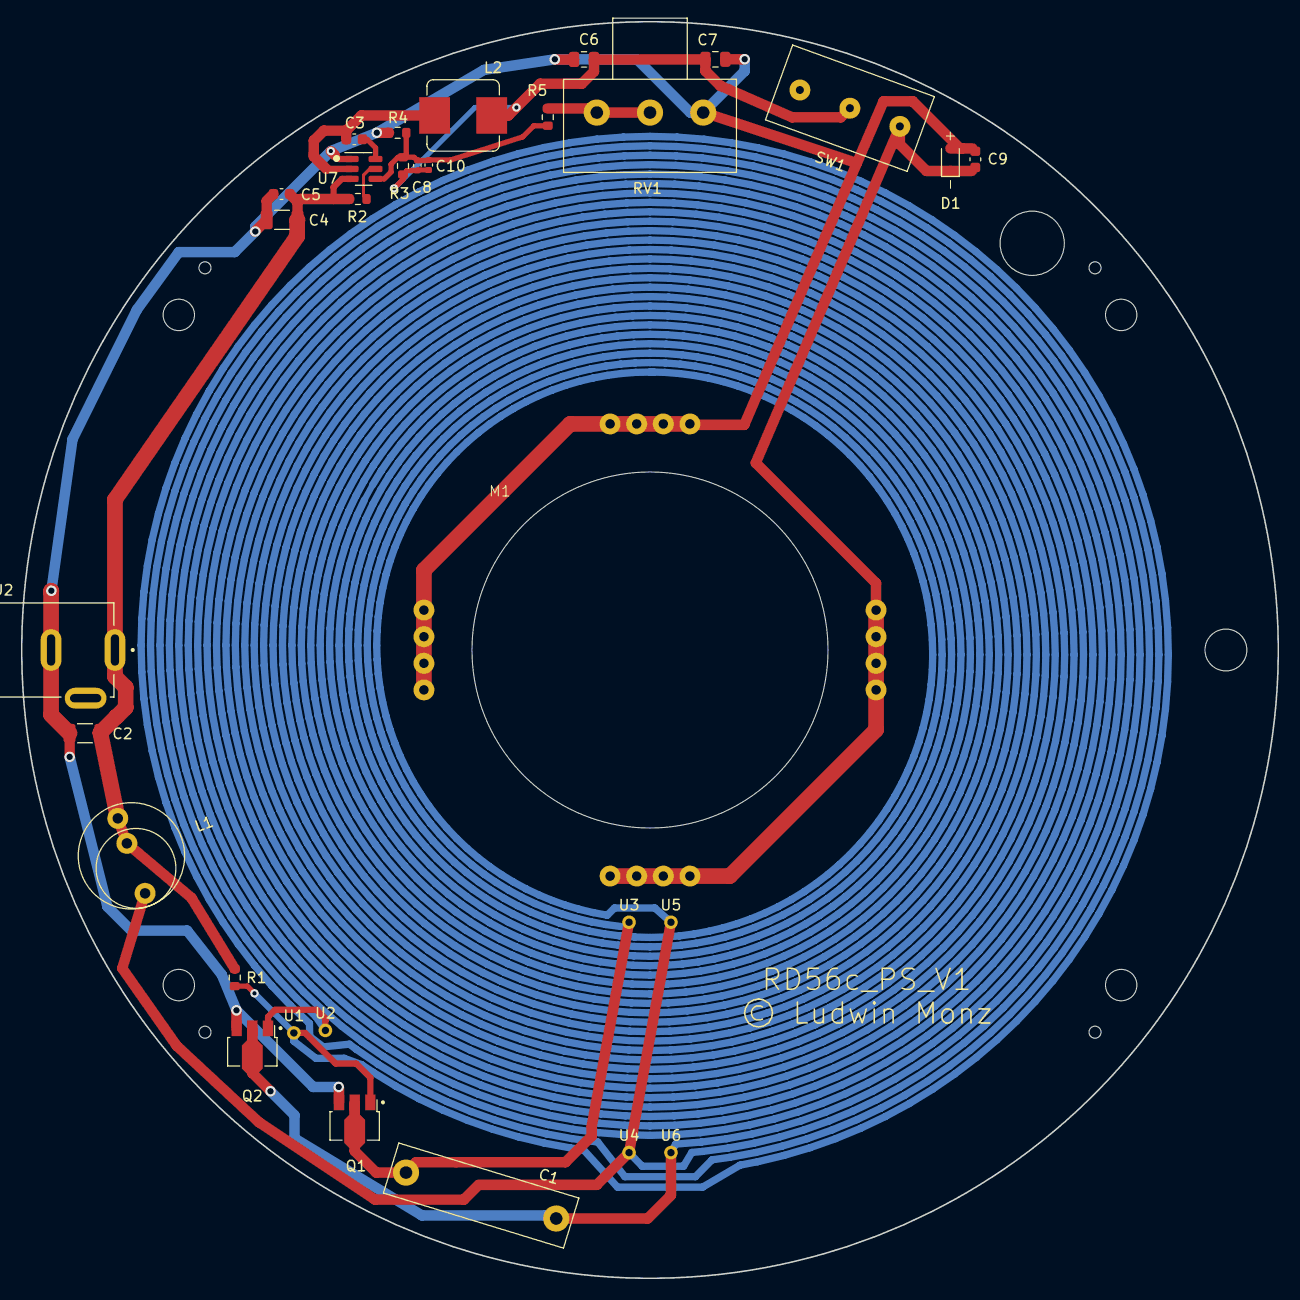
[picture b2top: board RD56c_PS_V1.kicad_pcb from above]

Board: 2 copper layers, 120.0 x 120.0 mm, 31 parts (0 on the bottom side), 11 nets.

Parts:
C1: 33nF; MKP10_630V
C2: 10µ, 50V; C_1206_3216Metric
C3, C5, C9: 100nF; C_0603_1608Metric
C4: 10µF, 50V; C_1206_3216Metric
C6, C7: 22µF, 25V; C_0805_2012Metric
C8: 47pF; C_0402_1005Metric
C10: 10pF; C_0402_1005Metric
D1: 1N5819
J2: Barrel_Jack_Switch_Pin3Ring; GRAVITECH_CON-SOCJ-2155
L1: 330µH; L_vertical12
L2: 33µH; L_Bourns_SRP7028A_7.3x6.6mm
M1: Motor_DC; motor_tray
Q1, Q2: D882
R1: 2k2; R_0603_1608Metric
R2, R3: 100k; R_0603_1608Metric
R4: 120k; R_0603_1608Metric
R5: 12k; R_0603_1608Metric
RV1: 100k; Poti_10mm
SW1: SW_DPDT_x2; Switch1
U1, U2, U3, U4, U5, U6: Pin-Connector; Pin_2mm
U7: TPS54202DDC; SOT-23-6

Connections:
+12V: C2.1, C4.1, C5.1, J2.1, L1.1, L1.3, R1.2, R2.1, U7.3 (VIN)
GND: C2.2, C4.2, C5.2, C6.2, C7.2, C9.2, D1.2 (A), J2.3, M1.2 (-), Q1.3 (E), Q2.3 (E), R4.2, RV1.1, U7.1 (GND)
unnamed: C9.1, D1.1 (K), M1.1 (+), SW1.3 (C)
unnamed: Q1.1 (B), Q2.1 (B), R1.1, U1.1 (Pin1), U2.1 (Pin1)
unnamed: C1.1, C1.2, L1.2, Q1.2 (C), Q2.2 (C), U3.1 (Pin1), U4.1 (Pin1), U5.1 (Pin1), U6.1 (Pin1)
unnamed: R5.2, RV1.2, RV1.3
unnamed: C6.1, C7.1, C8.1, C10.1, L2.2, R3.2, SW1.2 (B)
unnamed: C3.1, U7.6 (BOOT)
unnamed: R2.2, U7.5 (EN)
unnamed: C8.2, C10.2, R3.1, R4.1, R5.1, U7.4 (FB)
unnamed: C3.2, L2.1, U7.2 (SW)

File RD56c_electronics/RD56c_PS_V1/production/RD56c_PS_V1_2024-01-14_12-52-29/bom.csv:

Designator,Footprint,Quantity,Value,LCSC Part #
C1,MKP10_630V,1,33nF,
C10,0402,1,10pF,C32949
C2,1206,1,"10µ, 50V",C13585
"C3, C5, C9",0603,3,100nF,C14663
C4,1206,1,"10µF, 50V",C13585
"C6, C7",0805,2,"22µF, 25V",C45783
C8,0402,1,47pF,C1567
D1,1N5819,1,1N5819,C191023
J2,GRAVITECH_CON-SOCJ-2155,1,Barrel_Jack_Switch_Pin3Ring,
L1,L_vertical12,1,330µH,
L2,L_Bourns_SRP7028A_7.3x6.6mm,1,33µH,C177245
M1,motor_tray,1,Motor_DC,
"Q1, Q2",D882,2,D882,C9634
R1,0603,1,2k2,C4190
"R2, R3",0603,2,100k,C25803
R4,0603,1,120k,C25808
R5,0603,1,12k,C22790
RV1,Poti_10mm,1,100k,
SW1,Switch1,1,SW_DPDT_x2,
"U1, U2, U3, U4, U5, U6",Pin_2mm,6,Pin-Connector,
U7,SOT-23-6,1,TPS54202DDC,C191884

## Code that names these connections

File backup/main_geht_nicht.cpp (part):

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#include "hardware/pwm.h"
#include "hardware/spi.h"

#define PWM0_A 16					// enable R LEDs
#define PWM0_B 17					// enable G LEDs
#define PWM1_A 18					// enable B LEDs

#define SPI0_MISO 0					// LED SPI (STP24DP05)
#define SPI0_CSO 1					// RP2040 is SPI master
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#define DM 12
#define EF 13
#define TF 14
#define Hall 15						// Hall sensor input

#define lpt 3840;					// lines per turn (240 pixels x 16 subpixel)

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	gpio_set_dir(DM, true);
	gpio_put(DM, 1);

	gpio_init(Hall);
	gpio_set_dir(Hall, false);								// Hall is an input
	gpio_pull_up(Hall);										// switch on pull up resistor


// ====================================================================================================================
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//
// ====================================================================================================================

	gpio_init(PWM0_A);										// set gpio as output
	gpio_set_dir(PWM0_A, true);								//
	gpio_init(PWM0_B);										// set gpio as output
	gpio_set_dir(PWM0_B, true);								//
	gpio_init(PWM1_A);										// set gpio as output
	gpio_set_dir(PWM1_A, true);								//

	gpio_set_function(PWM0_A, GPIO_FUNC_PWM);				// enable PWM on 3 pins
	gpio_set_function(PWM0_B, GPIO_FUNC_PWM);
	gpio_set_function(PWM1_A, GPIO_FUNC_PWM);

	pwm_clear_irq(0);										// clear pwm interrupt
	pwm_set_irq_enabled(0, true);							// enable pwm interrupt
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//
// ====================================================================================================================

	gpio_set_function(Hall, GPIO_FUNC_SIO);								// software IO control (SIO)
	gpio_set_irq_enabled_with_callback(Hall, GPIO_IRQ_EDGE_FALL, true, &HallIRQ);

	Serial.begin(115200);
}
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void loop() {
	for (int i=0; i<100; i++) {
		Serial.print("Hello world ");
		Serial.println(gpio_get(Hall));
		delay(1000);
	}
	if (listing==true) {
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
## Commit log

2024-02-02 license added
2024-02-03 readme.md updated
2024-02-04 added copyright information
2024-02-04 BOM added
2024-02-10 new production files
2024-12-15 paths for gear.rdc and other files corrected
2024-12-17 bug fixes, mainly file browser. some new *rdc files in /data folder
2024-12-18 fix transformation matrix
2024-12-21 move from AsyncWebServer.h to WebServer.h to fix file upload bug. Extended javascripts.
2024-12-21 more animated images
2025-01-22 added empty_sheet.kicad_wks to KiCAD folders
2025-02-17 fixed compiling error - updated platformIO.ini
2025-02-20 fixed type conversion error. Thx @galmiklos
2025-03-19 added galmiklos' 3D printable case
2025-09-16 Remove tracked .DS_Store files and ignore them
2026-02-09 added some photos

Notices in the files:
RD56c_electronics/RD56c/RD56.kicad_pcb:
© Ludwin Monz
